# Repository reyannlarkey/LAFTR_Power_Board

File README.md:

# LAFTR_Power_Board
Eagle Files for the LAFTR power board

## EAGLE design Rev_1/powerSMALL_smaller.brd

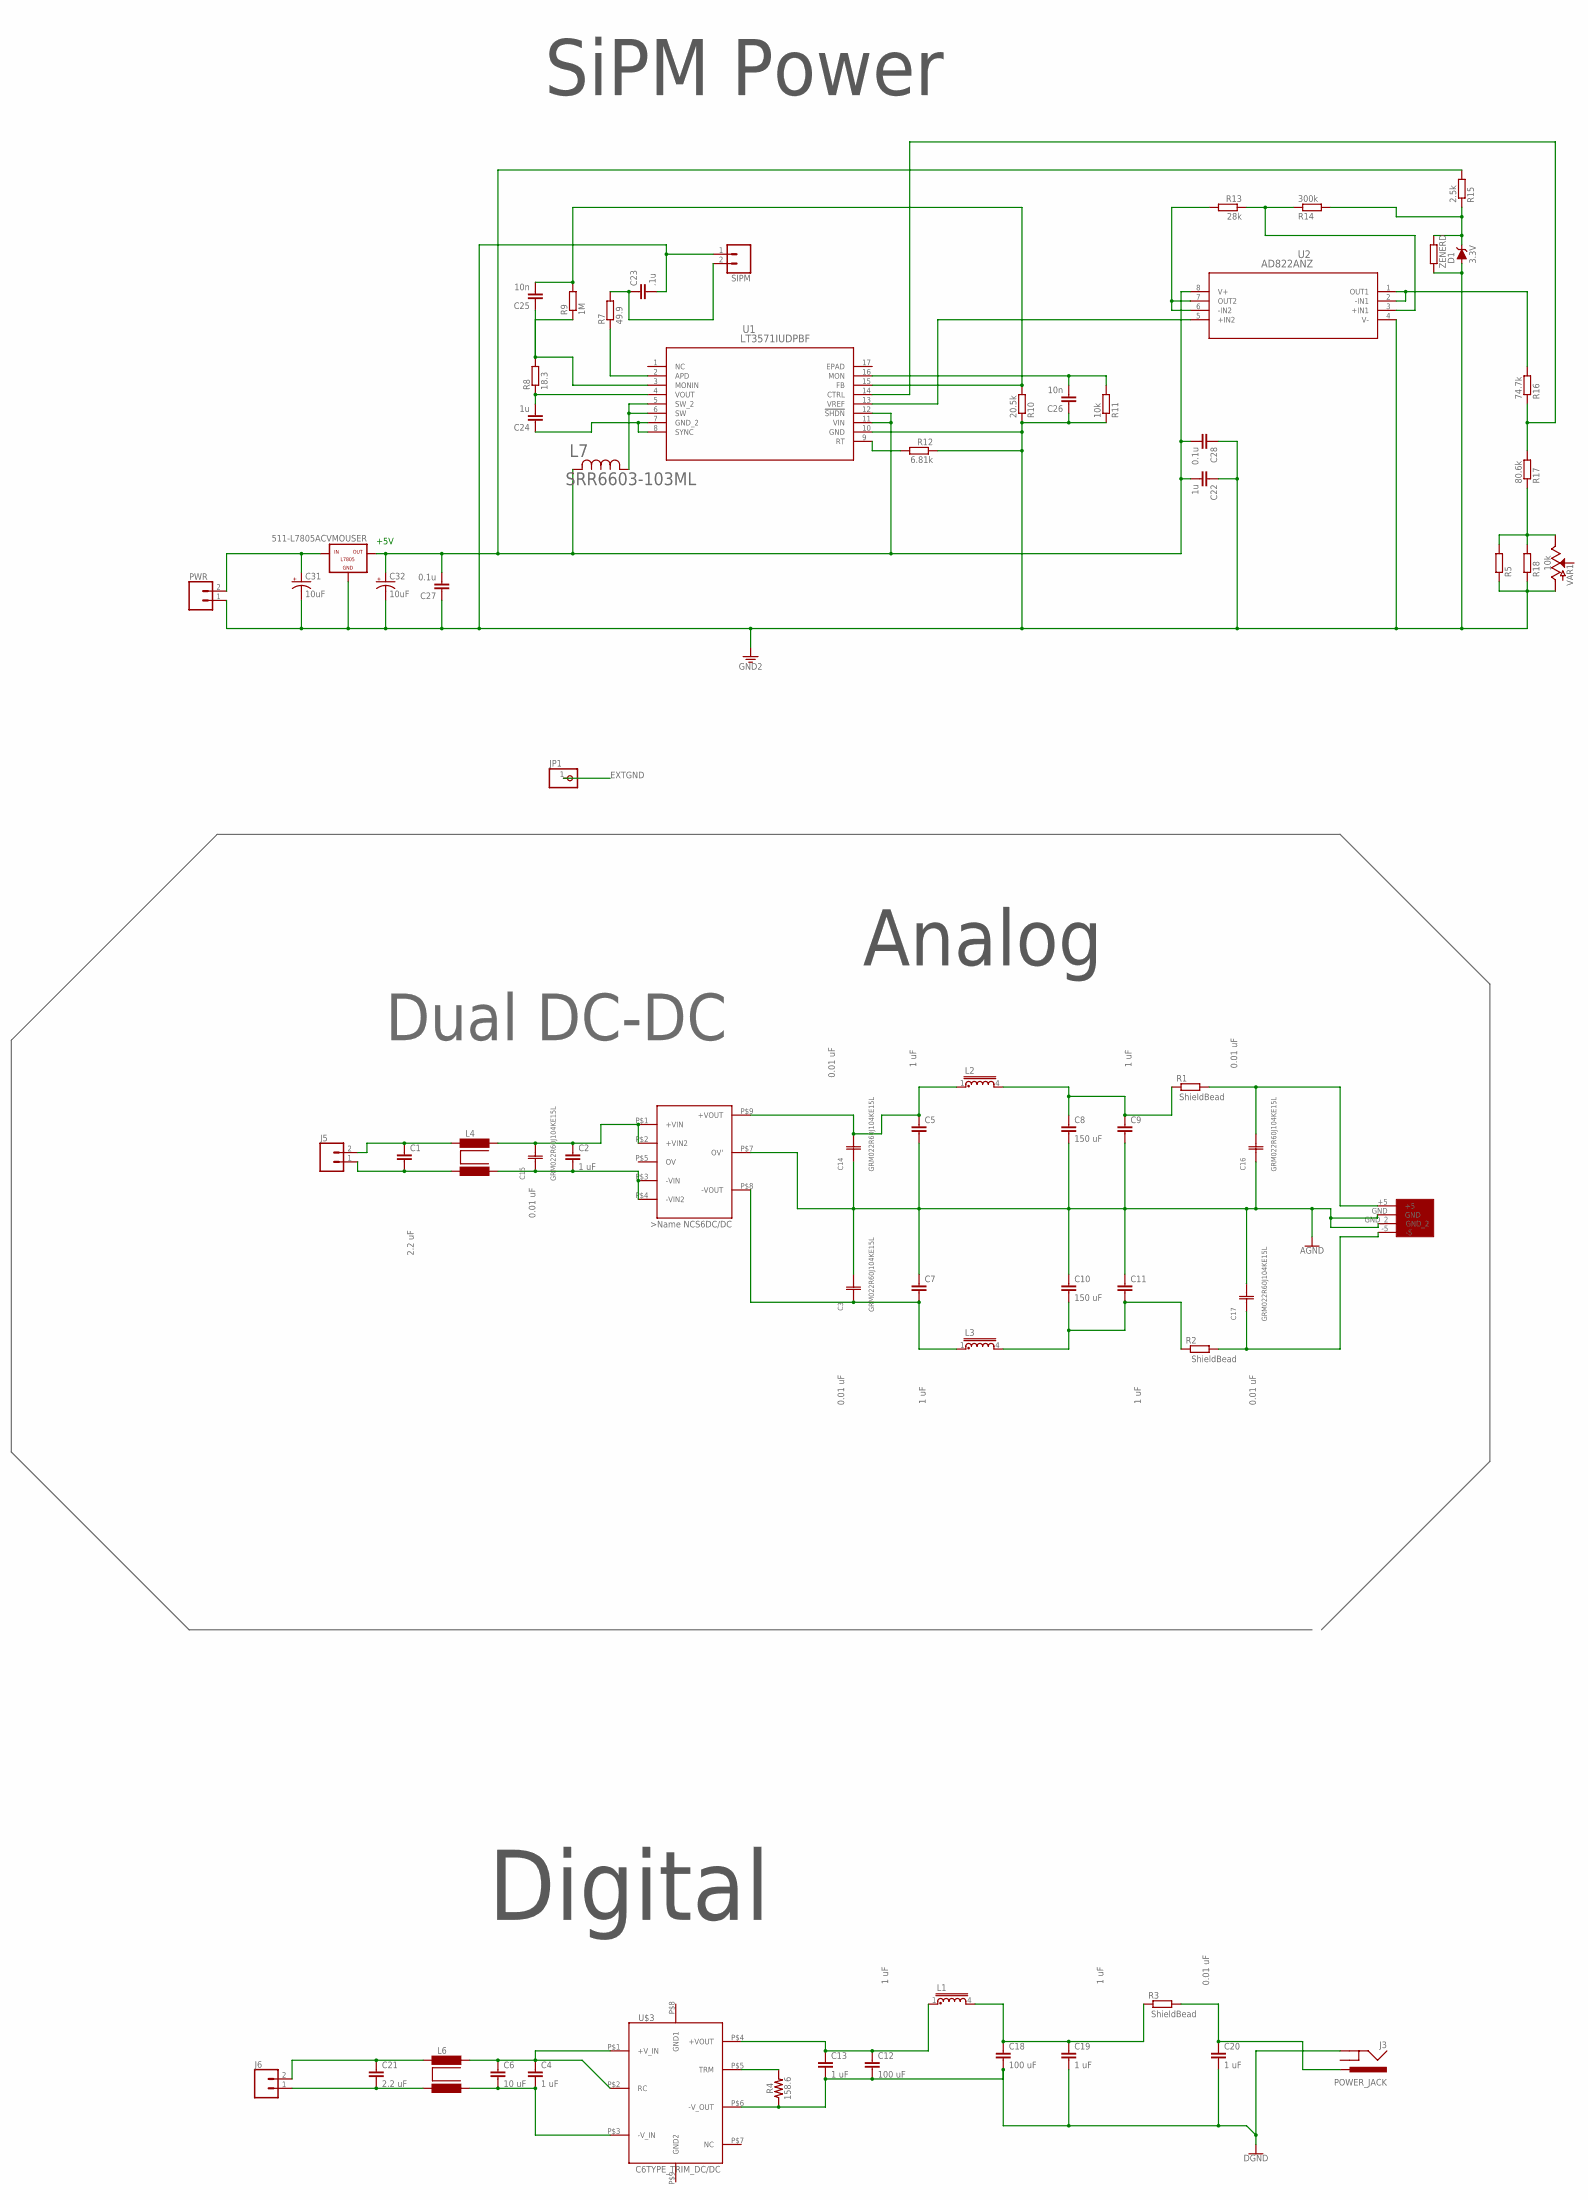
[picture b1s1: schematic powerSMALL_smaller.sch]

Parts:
511-L7805ACVMOUSER: -L7805; L7805
C1, C5, C7, C9, C11: C2.5/2; C2.5-2
C2, C4, C13, C19, C20: 1 uF; CAP-PTH-10MM
C3, C14, C15, C16, C17: GRM022R60J104KE15L; CAP_GRM02L_P42XP22
C6: 10 uF; CAP-PTH-10MM
C8, C10: 150 uF; CAP-PTH-10MM
C12, C18: 100 uF; CAP-PTH-10MM
C21: 2.2 uF; CAP-PTH-10MM
C22, C24: 1u; C2.5-2
C23: .1u; C2.5-2
C25, C26: 10n; C2.5-2
C27, C28: 0.1u; C2.5-2
C31, C32: 10uF; 0603-POLAR
D1: 3.3V; SOD-323
J3: POWER_JACK; POWER_JACK_PTH
J5, J6: CONN_02PTH4; 1X02_XTRA_BIG
JP1: PINHD-1X1; 1X01
L1, L2, L3: U15-CHOKE; U15CHOKE
L4, L6: SMR6-I; SM-R6
L7: SRR6603-103ML; IND_BOURNS_SRR6603
PWR: CONN_02PTH4; 1X02_XTRA_BIG
R1, R2, R3, R5, R18: R0207/10; 0207/10
R4: 158.6; AXIAL-0.3
R7: 49.9; 0207/10
R8: 18.3; 0207/10
R9: 1M; 0207/10
R10: 20.5k; 0207/10
R11: 10k; 0207/10
R12: 6.81k; 0207/10
R13: 28k; 0207/10
R14: 300k; 0207/10
R15: 2.5k; 0207/10
R16: 74.7k; 0207/10
R17: 80.6k; 0207/10
SIPM: CONN_02PTH4; 1X02_XTRA_BIG
U1: LT3571IUDPBF; QFN-16_UD
U2: AD822ANZ; N_8
U$1: NCS6D1205; NCS6D1205C
U$3: C6TYPE_TRIM_DC/DC; CONV/DC/DC_6W_SNGL_C6TYPE
U$4: WM403_NDPOWER_JACK; WM4302-ND
VAR1: 10k; POT-PTH-ALPS
ZENERD: R0207/10; 0207/10

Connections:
5VSUPPLY: 511-L7805ACVMOUSER.OUT, C22.2, C27.2, C28.2, C32.+, L7.2, R15.2, U1.11 (VIN), U1.12 (!SHDN), U2.8 (V+)
-FINV: C16.2 (22), R1.2, U$4.+5
AGND: C3.2 (22), C5.2, C7.1, C8.2, C9.2, C10.1, C11.1, C14.1 (11), C16.1 (11), C17.2 (22), U$1.P$7 (OV'), U$4.GND, U$4.GND_2
DGND: C12.2, C13.2, C18.2, C19.2, C20.2, J3.GND, R4.P$1 (1), U$3.P$6 (-V_OUT)
EXTGND: JP1.1
unnamed: C1.1, J5.2, L4.1
unnamed: C1.2, J5.1, L4.4
unnamed: C3.1 (11), C7.2, L3.1, U$1.P$8 (-VOUT)
unnamed: C2.1, C15.2 (22), L4.8, U$1.P$1 (+VIN), U$1.P$2 (+VIN2)
unnamed: C5.1, C14.2 (22), L2.1, U$1.P$9 (+VOUT)
unnamed: C8.1, C9.1, L2.4, R1.1
unnamed: R13.2, U2.6 (-IN2), U2.7 (OUT2)
unnamed: C10.2, C11.2, L3.4, R2.1
unnamed: C17.1 (11), R2.2, U$4.-5
unnamed: C21.1, J6.2, L6.1
unnamed: C21.2, J6.1, L6.4
unnamed: C4.1, C6.1, L6.8, U$3.P$1 (+V_IN), U$3.P$2 (RC)
unnamed: C4.2, C6.2, L6.5, U$3.P$3 (-V_IN)
unnamed: C24.2, R8.1, U1.4 (VOUT)
unnamed: C20.1, J3.PWR, R3.2
unnamed: R4.P$2 (2), U$3.P$5 (TRM)
unnamed: C18.1, C19.1, L1.4, R3.1
unnamed: C24.1, U1.7 (GND_2), U1.8 (SYNC)
unnamed: C12.1, C13.1, L1.1, U$3.P$4 (+VOUT)
unnamed: R7.1, U1.2 (APD)
unnamed: C23.1, R7.2, SIPM.2
unnamed: C25.1, R8.2, R9.1, U1.3 (MONIN)
unnamed: C26.2, R11.2, U1.16 (MON)
unnamed: L7.1, U1.5 (SW_2), U1.6 (SW)
unnamed: U1.13 (VREF), U2.5 (+IN2)
unnamed: R16.2, U2.1 (OUT1), U2.2 (-IN1)
unnamed: C25.2, R9.2, R10.2, U1.15 (FB)
unnamed: R13.1, R14.1, U2.3 (+IN1)
unnamed: R12.2, U1.9 (RT)
unnamed: D1.C, R14.2, R15.1, ZENERD.2
unnamed: R16.1, R17.2, U1.14 (CTRL)
unnamed: R5.2, R17.1, R18.2, VAR1.P$1 (E)
unnamed: C2.2, C15.1 (11), L4.5, U$1.P$3 (-VIN), U$1.P$4 (-VIN2)
unnamed: 511-L7805ACVMOUSER.IN, C31.+, PWR.2
SIPMGND: 511-L7805ACVMOUSER.GND, C22.1, C23.2, C26.1, C27.1, C28.1, C31.-, C32.-, D1.A, PWR.1, R5.1, R10.1, R11.1, R12.1, R18.1, SIPM.1, U1.10 (GND), U2.4 (V-), VAR1.P$3 (A), ZENERD.1

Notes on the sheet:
0.01 uF
2.2 uF
1 uF
ShieldBead
Dual DC-DC
Analog
Digital
SiPM Power
+5V

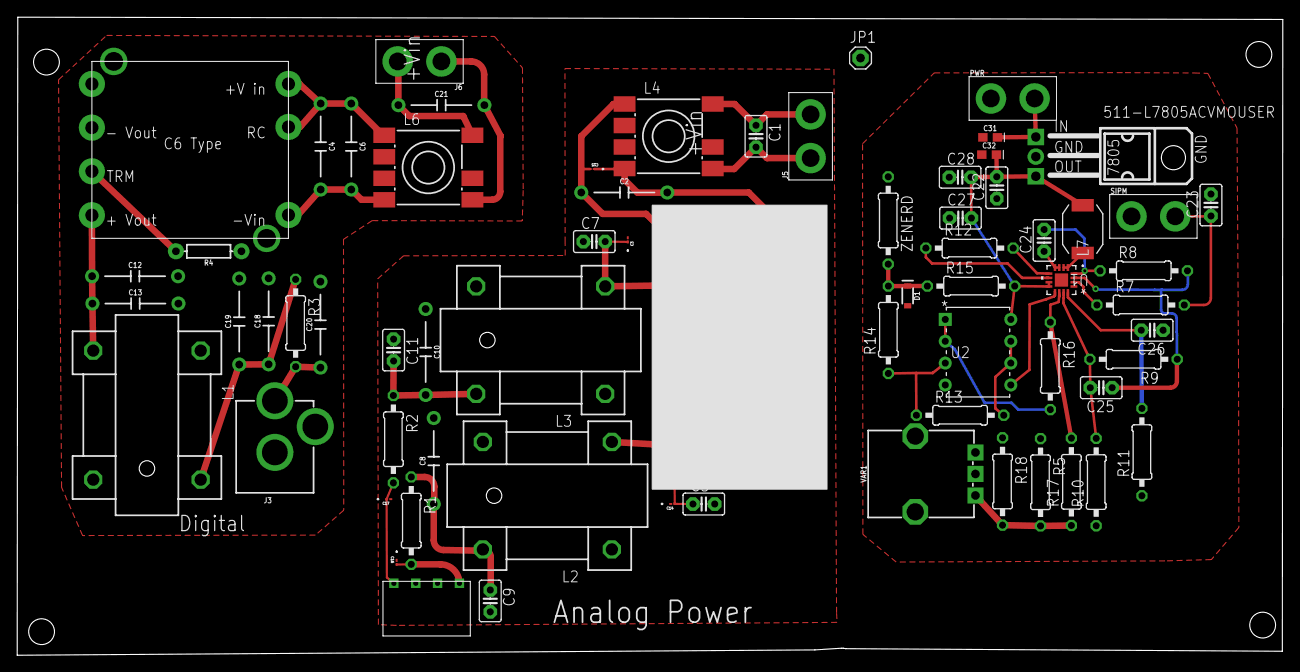
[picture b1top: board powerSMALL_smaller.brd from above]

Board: 4 copper layers, 147.2 x 74.2 mm, 68 parts (0 on the bottom side), 39 nets.

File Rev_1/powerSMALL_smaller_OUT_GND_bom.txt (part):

Partlist exported from /home/reyannlarkey/Desktop/LAFTR_POWER/powerSMALL_smaller_OUT_GND.sch at 6/26/18 3:15 PM

Qty Value              Device                          Package                   Parts                     Description                                                                                                     
4                      CONN_02PTH4                     1X02_XTRA_BIG             J5, J6, PWR, SIPM         Multi connection point. Often used as Generic Header-pin footprint for 0.1 inch spaced/style header connections 
1                      PINHD-1X1                       1X01                      JP1                       Pin header 1x1 for 0.1" spacing                                                                                 
1                      R0207/10                        0207/10                   ZENERD                    RESISTOR, European symbol                                                                                       
2                      SMR6-I                          SM-R6                     L4, L6                    CHOKE                                                                                                           
3                      U15-CHOKE                       U15CHOKE                  L1, L2, L3                CHOKE                                                                                                           
1   -L7805             -L7805                          L7805                     511-L7805ACVMOUSER                                                                                                                        
1   .1uF               C2.5/2                          C2.5-2                    C23                       CAPACITOR                                                                                                       
5   0.01uF             10NF-PTH-10MM-10000V-1-%        CAP-PTH-10MM              C2, C4, C13, C19, C20     0.01uF/10nF/10,000pF ceramic capacitors                                                                         
5   0.01uF             C-EUC0603                       C0603                     C29, C30, C33, C34, C35   CAPACITOR, European symbol                                                                                      
2   0.1uF              C2.5/2                          C2.5-2                    C27, C28                  CAPACITOR                                                                                                       
2   100uF              10NF-PTH-10MM-10000V-1-%        CAP-PTH-10MM              C12, C18                  0.01uF/10nF/10,000pF ceramic capacitors                                                                         
1   10k                POTENTIOMETER-PTH-9MM-1/20W-20% POT-PTH-ALPS              VAR1                      Potentiometer (Pot)                                                                                             
1   10k                R0207/10                        0207/10                   R11                       RESISTOR, European symbol                                                                                       
2   10nF               C2.5/2                          C2.5-2                    C25, C26                  CAPACITOR                                                                                                       
1   10uF               10NF-PTH-10MM-10000V-1-%        CAP-PTH-10MM              C6                        0.01uF/10nF/10,000pF ceramic capacitors                                                                         
2   10uF               10UF-POLAR-0603-6.3V-20%(TANT)  0603-POLAR                C31, C32                  10.0µF polarized capacitors                                                                                     
2   150 uF             10NF-PTH-10MM-10000V-1-%        CAP-PTH-10MM              C8, C10                   0.01uF/10nF/10,000pF ceramic capacitors                                                                         
1   158.6              10MOHM-HORIZ-1/4W-5%            AXIAL-0.3                 R4                        RES-09327                                                                                                       
1   18.3               R0207/10                        0207/10                   R8                        RESISTOR, European symbol                                                                                       
1   1M                 R0207/10                        0207/10                   R9                        RESISTOR, European symbol                                                                                       
6   1uF                C2.5/2                          C2.5-2                    C5, C7, C9, C11, C22, C24 CAPACITOR                                                                                                       
1   2.2uF              10NF-PTH-10MM-10000V-1-%        CAP-PTH-10MM              C21                       0.01uF/10nF/10,000pF ceramic capacitors                                                                         
1   2.2uF              C2.5/2                          C2.5-2                    C1                        CAPACITOR                                                                                                       
1   2.5k               R0207/10                        0207/10                   R15                       RESISTOR, European symbol                                                                                       
1   20.5k              R0207/10                        0207/10                   R10                       RESISTOR, European symbol                                                                                       
1   28k                R0207/10                        0207/10                   R13                       RESISTOR, European symbol                                                                                       
1   3.3V               DIODE-ZENER-MM3Z3V3T1G          SOD-323                   D1                        Zener Diode                                                                                                     
1   300k               R0207/10                        0207/10                   R14                       RESISTOR, European symbol                                                                                       
1   49.9               R0207/10                        0207/10                   R7                        RESISTOR, European symbol                                                                                       
1   6.81k              R0207/10                        0207/10                   R12                       RESISTOR, European symbol                                                                                       
1   74.7k              R0207/10                        0207/10                   R16                       RESISTOR, European symbol                                                                                       
1   80.6k              R0207/10                        0207/10                   R17                       RESISTOR, European symbol                                                                                       
1   AD822ANZ           AD822ANZ                        N_8                       U2                                                                                                                                        
1   C6TYPE_TRIM_DC/DC  C6TYPE_TRIM_DC/DC               CONV/DC/DC_6W_SNGL_C6TYPE U$3                                                                                                                                       
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
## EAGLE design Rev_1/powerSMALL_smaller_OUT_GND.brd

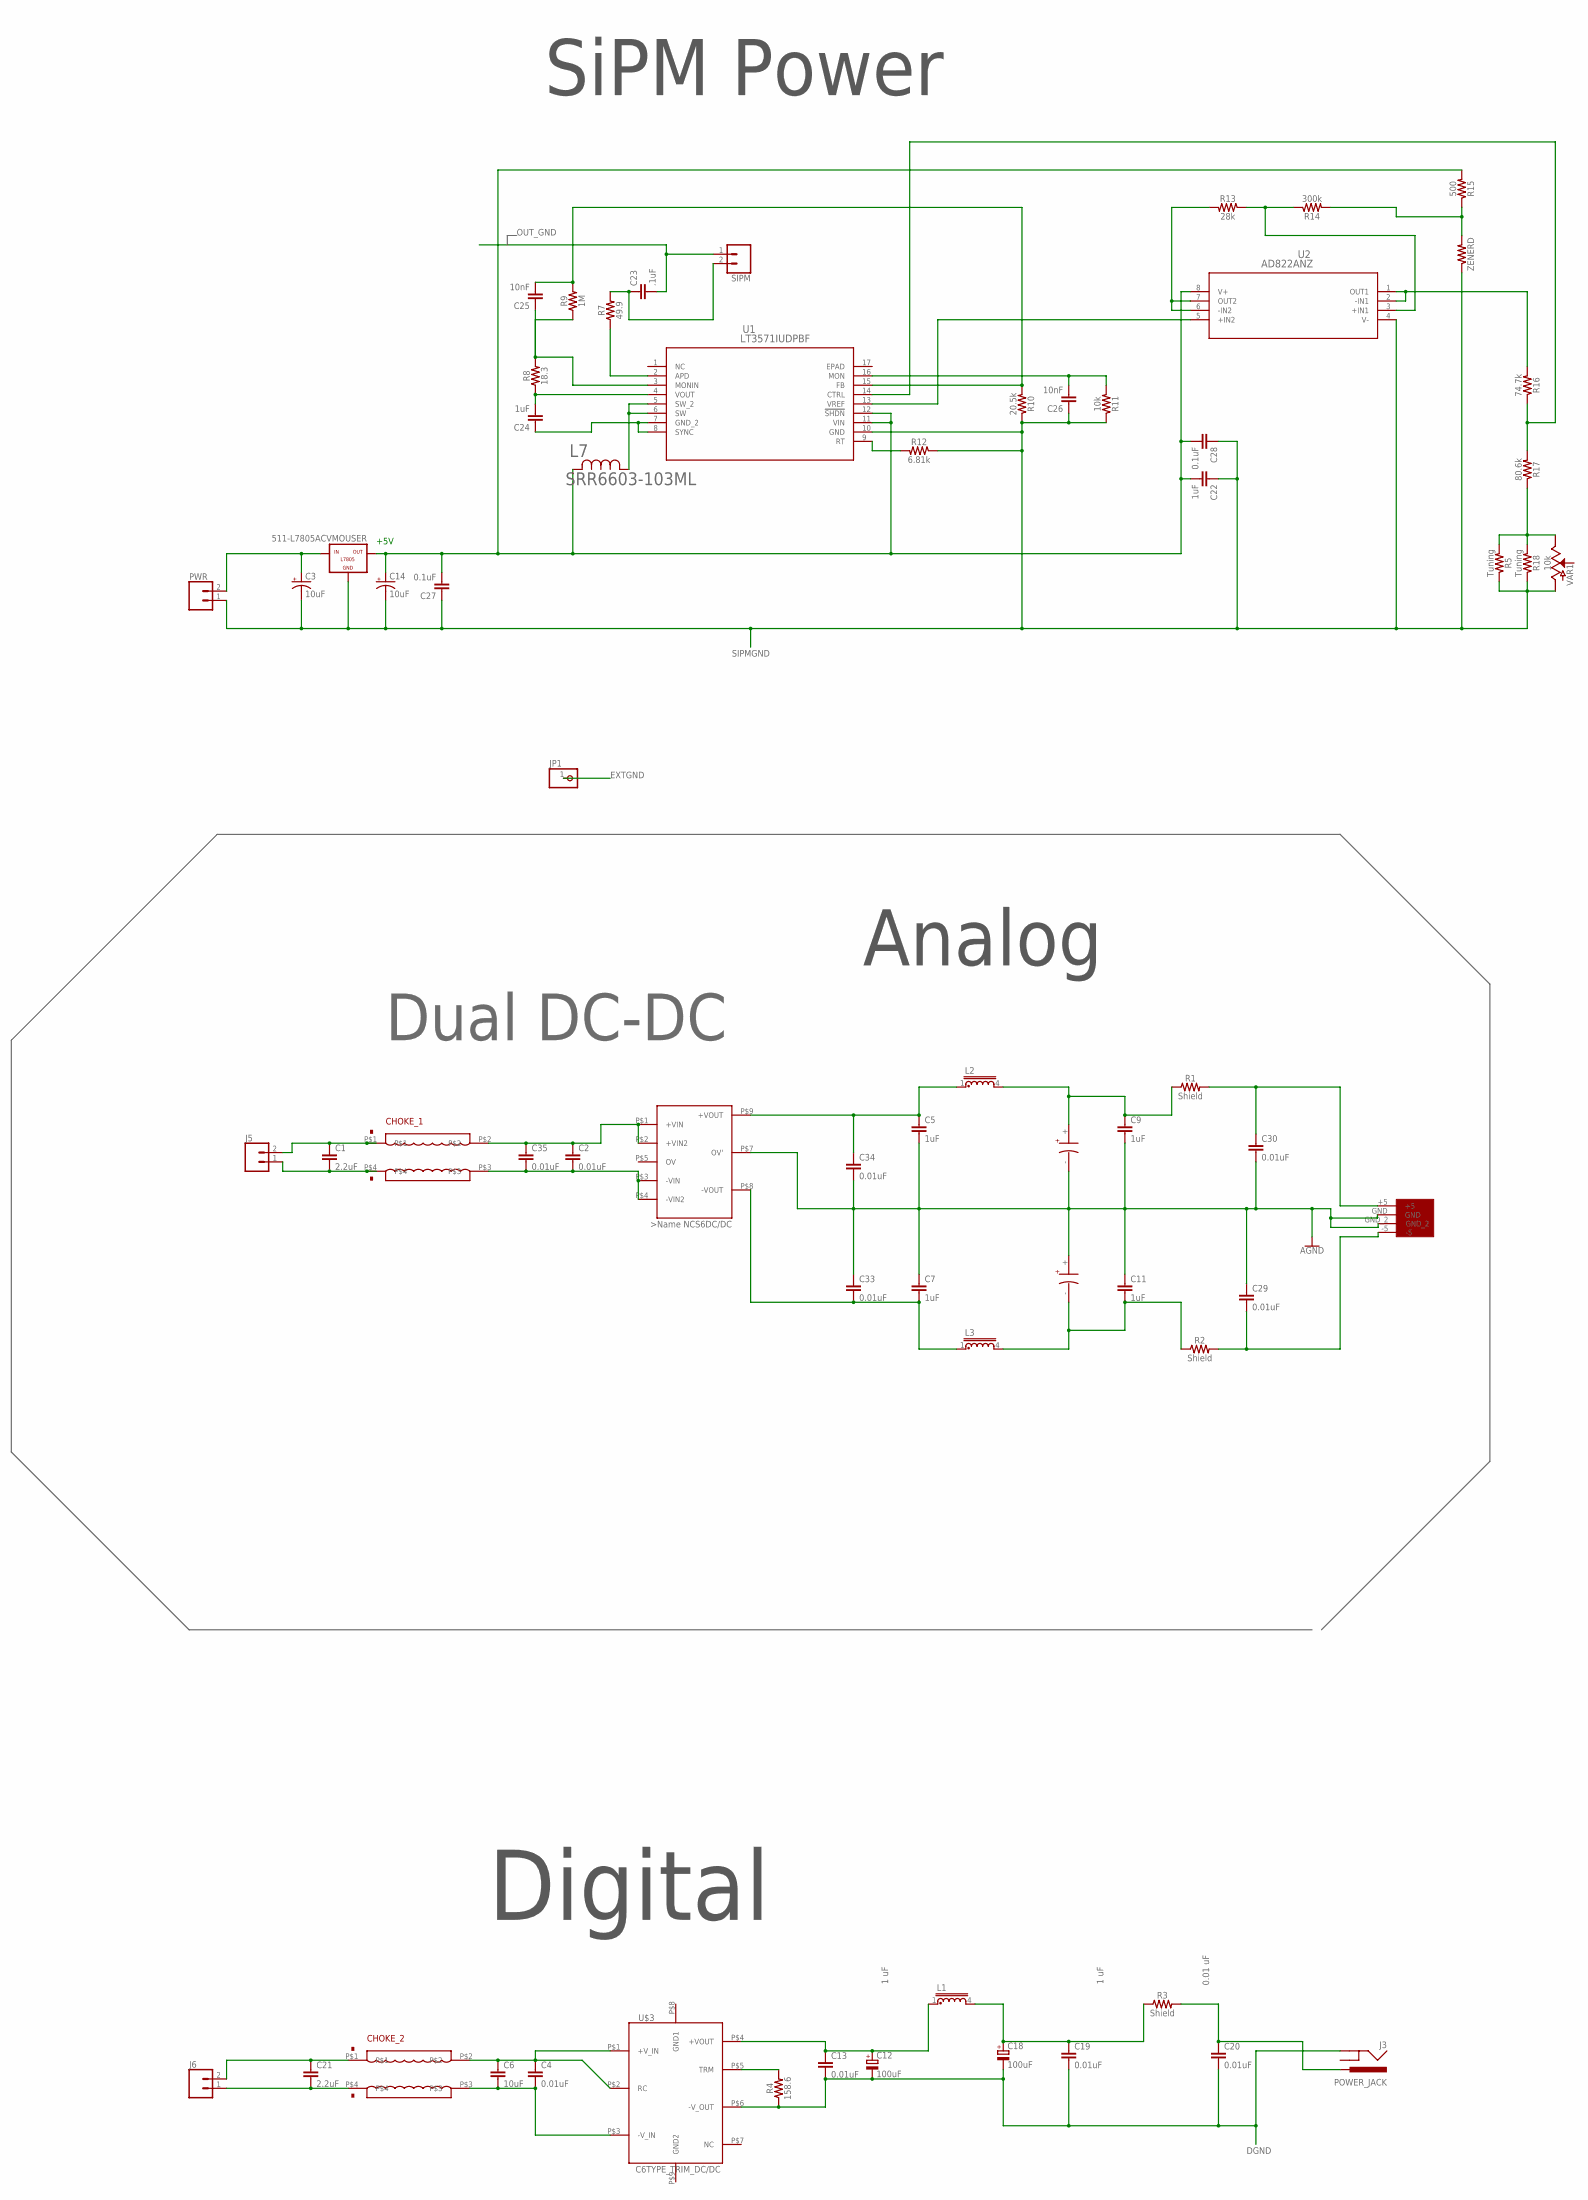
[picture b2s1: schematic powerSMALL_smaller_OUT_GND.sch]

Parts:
511-L7805ACVMOUSER: -L7805; L7805
C1, C21: 2.2uF; C050-024X044
C2, C4, C13, C19, C20: 0.01uF; C025-025X050
C3, C14: 10uF; T/3528-12R
C5, C7, C9, C11, C22, C24: 1uF; C025-025X050
C6: 10uF; C025-025X050
C8, C10: 150uF; 399-3567-ND150UF
C12, C18: 100uF; C/6032-28R
C23: .1uF; C2.5-2
C25, C26: 10nF; C2.5-2
C27, C28: 0.1uF; C2.5-2
C29, C30, C33, C34, C35: 0.01uF; C0603
CHOKE_1, CHOKE_2: DN4730-ND
J3: POWER_JACK; POWER_JACK_PTH
J5, J6: CONN_02PTH4; 1X02_XTRA_BIG
JP1: PINHD-1X1; 1X01
L1, L2, L3: U15-CHOKE; U15CHOKE
L7: SRR6603-103ML; IND_BOURNS_SRR6603
PWR: CONN_02PTH4; 1X02_XTRA_BIG
PWR_JACK: WM403_NDPOWER_JACK; WM4302-ND
R1, R2, R3: Shield; AXIAL-0.3
R4: 158.6; AXIAL-0.3
R5, R18: Tuning; AXIAL-0.3
R7: 49.9; AXIAL-0.3
R8: 18.3; AXIAL-0.3
R9: 1M; AXIAL-0.3
R10: 20.5k; AXIAL-0.3
R11: 10k; AXIAL-0.3
R12: 6.81k; AXIAL-0.3
R13: 28k; AXIAL-0.3
R14: 300k; AXIAL-0.3
R15: 500; AXIAL-0.3
R16: 74.7k; AXIAL-0.3
R17: 80.6k; AXIAL-0.3
SIPM: CONN_02PTH4; 1X02_XTRA_BIG
U1: LT3571IUDPBF; QFN-16_UD
U2: AD822ANZ; N_8
U$1: NCS6D1205; NCS6D1205C
U$3: C6TYPE_TRIM_DC/DC; CONV/DC/DC_6W_SNGL_C6TYPE
VAR1: 10k; POT-PTH-ALPS
ZENERD: AXIAL-0.3

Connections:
5VSUPPLY: 511-L7805ACVMOUSER.OUT, C14.+, C22.2, C27.2, C28.2, L7.2, R15.P$2 (2), U1.11 (VIN), U1.12 (!SHDN), U2.8 (V+)
-FINV: C30.1, PWR_JACK.+5, R1.P$2 (2)
AGND: C5.2, C7.1, C8.- (N), C9.2, C10.+, C11.1, C29.1, C30.2, C33.1, C34.2, PWR_JACK.GND, PWR_JACK.GND_2, U$1.P$7 (OV')
DGND: C12.-, C13.2, C18.-, C19.2, C20.2, J3.GND, R4.P$1 (1), U$3.P$6 (-V_OUT)
EXTGND: JP1.1
unnamed: C1.1, CHOKE_1.P$1, J5.2
unnamed: C1.2, CHOKE_1.P$4, J5.1
unnamed: C7.2, C33.2, L3.1, U$1.P$8 (-VOUT)
unnamed: C2.1, C35.1, CHOKE_1.P$2, U$1.P$1 (+VIN), U$1.P$2 (+VIN2)
unnamed: C8.+, C9.1, L2.4, R1.P$1 (1)
unnamed: R13.P$2 (2), U2.6 (-IN2), U2.7 (OUT2)
unnamed: C10.- (N), C11.2, L3.4, R2.P$1 (1)
unnamed: C29.2, PWR_JACK.-5, R2.P$2 (2)
unnamed: C21.1, CHOKE_2.P$1, J6.2
unnamed: C21.2, CHOKE_2.P$4, J6.1
unnamed: C4.1, C6.1, CHOKE_2.P$2, U$3.P$1 (+V_IN), U$3.P$2 (RC)
unnamed: C4.2, C6.2, CHOKE_2.P$3, U$3.P$3 (-V_IN)
unnamed: C24.2, R8.P$1 (1), U1.4 (VOUT)
unnamed: C20.1, J3.PWR, R3.P$2 (2)
unnamed: R4.P$2 (2), U$3.P$5 (TRM)
unnamed: C18.+, C19.1, L1.4, R3.P$1 (1)
unnamed: C24.1, U1.7 (GND_2), U1.8 (SYNC)
unnamed: C12.+, C13.1, L1.1, U$3.P$4 (+VOUT)
unnamed: R7.P$1 (1), U1.2 (APD)
unnamed: C23.1, R7.P$2 (2), SIPM.2
unnamed: C25.1, R8.P$2 (2), R9.P$1 (1), U1.3 (MONIN)
unnamed: C26.2, R11.P$2 (2), U1.16 (MON)
unnamed: L7.1, U1.5 (SW_2), U1.6 (SW)
unnamed: U1.13 (VREF), U2.5 (+IN2)
unnamed: C5.1, C34.1, L2.1, U$1.P$9 (+VOUT)
unnamed: R16.P$2 (2), U2.1 (OUT1), U2.2 (-IN1)
unnamed: C25.2, R9.P$2 (2), R10.P$2 (2), U1.15 (FB)
unnamed: R13.P$1 (1), R14.P$1 (1), U2.3 (+IN1)
unnamed: R12.P$2 (2), U1.9 (RT)
unnamed: R14.P$2 (2), R15.P$1 (1), ZENERD.P$2 (2)
unnamed: R16.P$1 (1), R17.P$2 (2), U1.14 (CTRL)
unnamed: R5.P$2 (2), R17.P$1 (1), R18.P$2 (2), VAR1.P$1 (E)
unnamed: C2.2, C35.2, CHOKE_1.P$3, U$1.P$3 (-VIN), U$1.P$4 (-VIN2)
unnamed: 511-L7805ACVMOUSER.IN, C3.+, PWR.2
OUT_GND: C23.2, SIPM.1
SIPMGND: 511-L7805ACVMOUSER.GND, C3.-, C14.-, C22.1, C26.1, C27.1, C28.1, PWR.1, R5.P$1 (1), R10.P$1 (1), R11.P$1 (1), R12.P$1 (1), R18.P$1 (1), U1.10 (GND), U2.4 (V-), VAR1.P$3 (A), ZENERD.P$1 (1)

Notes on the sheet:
Dual DC-DC
0.01 uF
1 uF
Analog
Digital
SiPM Power
+5V

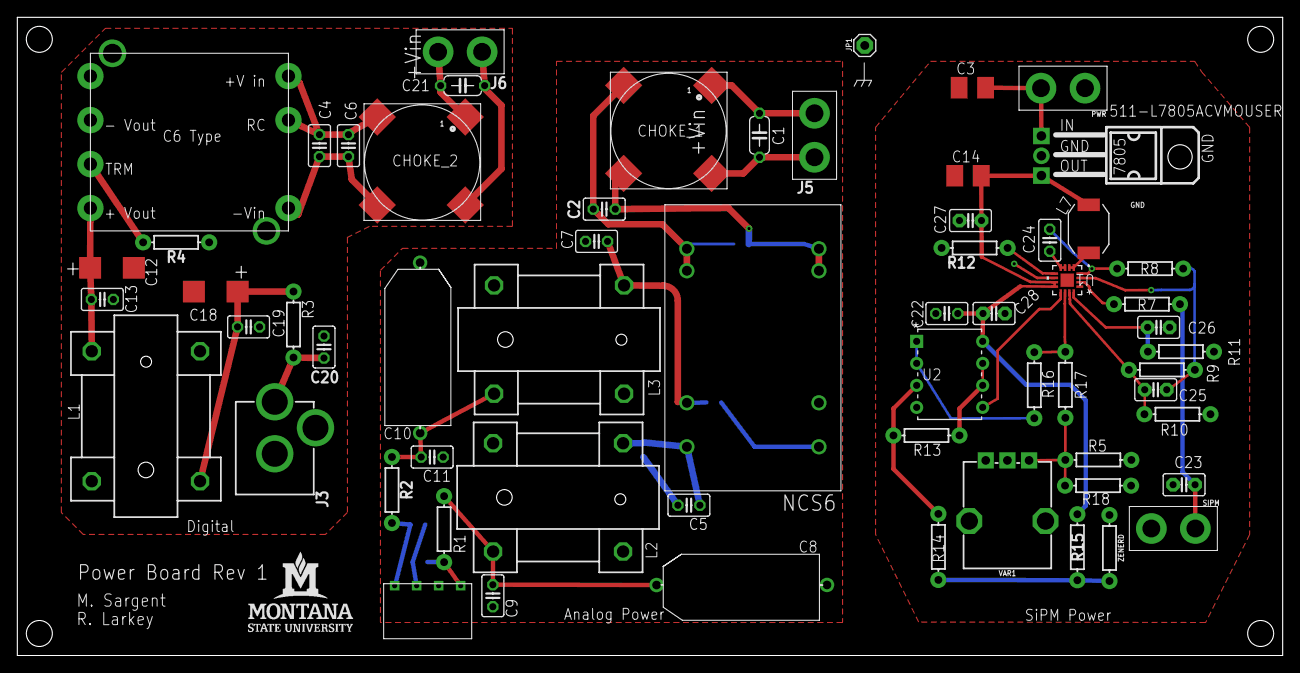
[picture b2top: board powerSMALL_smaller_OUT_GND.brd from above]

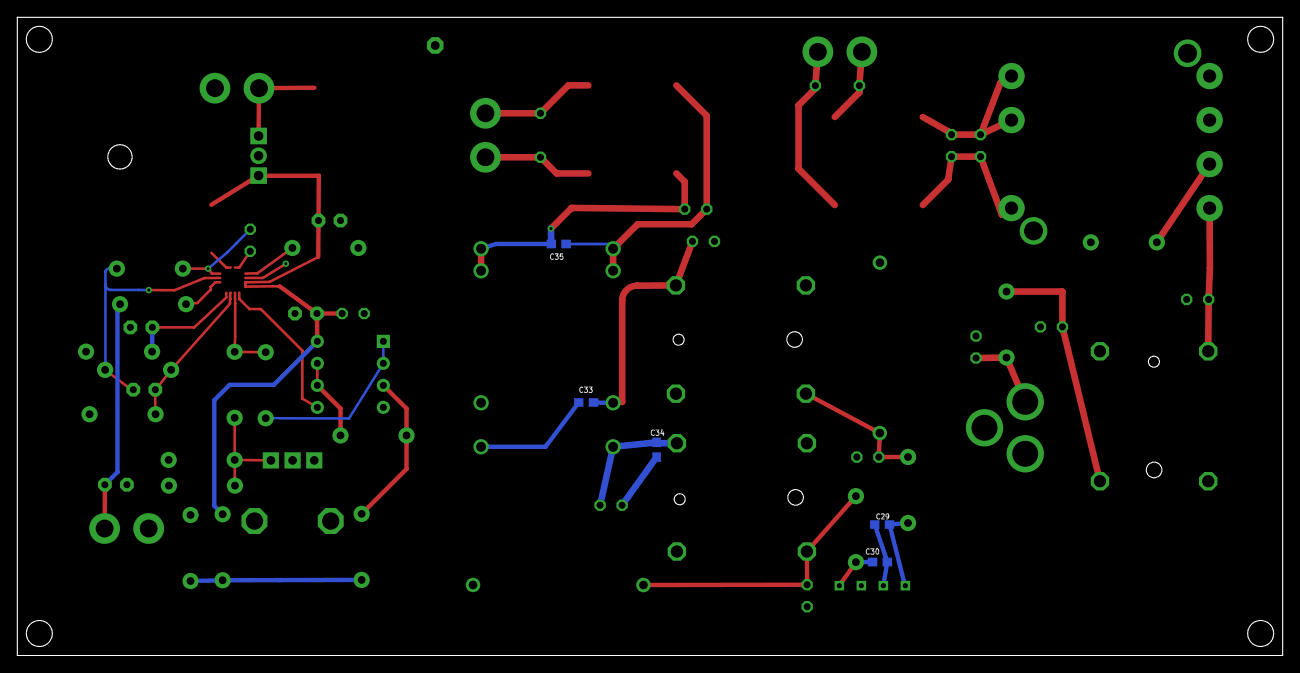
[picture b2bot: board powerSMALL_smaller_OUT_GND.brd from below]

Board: 4 copper layers, 146.1 x 73.7 mm, 67 parts (5 on the bottom side), 40 nets.

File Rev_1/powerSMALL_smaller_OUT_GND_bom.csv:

"Qty";"Value";"Device";"Package";"Parts";"Description";"MANUFACTURER_PART_NUMBER";"MF";"MPN";"OC_FARNELL";"OC_NEWARK";"PROD_ID";"SF_SKU";"SPICEMODEL";"SPICEPREFIX";"VALUE";"VENDOR";
"4";"";"CONN_02PTH4";"1X02_XTRA_BIG";"J5, J6, PWR, SIPM";"Multi connection point. Often used as Generic Header-pin footprint for 0.1 inch spaced/style header connections";"";"";"";"";"unknown";"";"";"";"";"";"";
"1";"";"PINHD-1X1";"1X01";"JP1";"Pin header 1x1 for 0.1" spacing";"";"";"";"";"unknown";"";"";"";"";"";"";
"1";"";"R0207/10";"0207/10";"ZENERD";"RESISTOR, European symbol";"";"";"";"";"unknown";"";"";"NONE";"R";"";"";
"2";"";"SMR6-I";"SM-R6";"L4, L6";"CHOKE";"";"";"";"unknown";"unknown";"";"";"";"";"";"";
"3";"";"U15-CHOKE";"U15CHOKE";"L1, L2, L3";"CHOKE";"";"";"";"unknown";"unknown";"";"";"";"";"";"";
"1";"-L7805";"-L7805";"L7805";"511-L7805ACVMOUSER";"";"";"";"";"";"unknown";"";"";"";"";"";"";
"1";".1uF";"C2.5/2";"C2.5-2";"C23";"CAPACITOR";"";"";"";"";"unknown";"";"";"";"";"";"";
"1";"0.01uF";"C-EU025-024X044";"C025-024X044";"C2";"CAPACITOR, European symbol";"";"";"";"";"unknown";"";"";"";"";"";"";
"4";"0.01uF";"C-EU025-025X050";"C025-025X050";"C4, C13, C19, C20";"CAPACITOR, European symbol";"";"";"";"";"unknown";"";"";"";"";"";"";
"5";"0.01uF";"C-EUC0603";"C0603";"C29, C30, C33, C34, C35";"CAPACITOR, European symbol";"";"";"";"";"";"";"";"";"";"";"";
"2";"0.1uF";"C2.5/2";"C2.5-2";"C27, C28";"CAPACITOR";"";"";"";"";"unknown";"";"";"";"";"";"";
"2";"100uF";"C-EU025-025X050";"C025-025X050";"C12, C18";"CAPACITOR, European symbol";"";"";"";"";"unknown";"";"";"";"";"";"";
"1";"10k";"POTENTIOMETER-PTH-9MM-1/20W-20%";"POT-PTH-ALPS";"VAR1";"Potentiometer (Pot)";"";"";"";"";"unknown";"RES-09177";"COM-09288";"";"";"10k";"";
"1";"10k";"R0207/10";"0207/10";"R11";"RESISTOR, European symbol";"";"";"";"";"unknown";"";"";"NONE";"R";"";"";
"2";"10nF";"C2.5/2";"C2.5-2";"C25, C26";"CAPACITOR";"";"";"";"";"unknown";"";"";"";"";"";"";
"2";"10uF";"10UF-POLAR-0603-6.3V-20%(TANT)";"0603-POLAR";"C31, C32";"10.0µF polarized capacitors";"";"";"";"";"unknown";"CAP-13210";"";"";"";"10uF";"";
"1";"10uF";"C-EU025-025X050";"C025-025X050";"C6";"CAPACITOR, European symbol";"";"";"";"";"unknown";"";"";"";"";"";"";
"2";"150 uF";"C-EU025-025X050";"C025-025X050";"C8, C10";"CAPACITOR, European symbol";"";"";"";"";"unknown";"";"";"";"";"";"";
"1";"158.6";"10MOHM-HORIZ-1/4W-5%";"AXIAL-0.3";"R4";"RES-09327";"";"";"";"";"unknown";"RES-09327";"";"";"";"10M";"";
"1";"18.3";"R0207/10";"0207/10";"R8";"RESISTOR, European symbol";"";"";"";"";"unknown";"";"";"NONE";"R";"";"";
"1";"1M";"R0207/10";"0207/10";"R9";"RESISTOR, European symbol";"";"";"";"";"unknown";"";"";"NONE";"R";"";"";
"6";"1uF";"C2.5/2";"C2.5-2";"C5, C7, C9, C11, C22, C24";"CAPACITOR";"";"";"";"";"unknown";"";"";"";"";"";"";
"1";"2.2uF";"C-EU025-025X050";"C025-025X050";"C21";"CAPACITOR, European symbol";"";"";"";"";"unknown";"";"";"";"";"";"";
"1";"2.2uF";"C2.5/2";"C2.5-2";"C1";"CAPACITOR";"";"";"";"";"unknown";"";"";"";"";"";"";
"1";"2.5k";"R0207/10";"0207/10";"R15";"RESISTOR, European symbol";"";"";"";"";"unknown";"";"";"NONE";"R";"";"";
"1";"20.5k";"R0207/10";"0207/10";"R10";"RESISTOR, European symbol";"";"";"";"";"unknown";"";"";"NONE";"R";"";"";
"1";"28k";"R0207/10";"0207/10";"R13";"RESISTOR, European symbol";"";"";"";"";"unknown";"";"";"NONE";"R";"";"";
"1";"3.3V";"DIODE-ZENER-MM3Z3V3T1G";"SOD-323";"D1";"Zener Diode";"";"";"";"";"unknown";"DIO-11284";"";"";"";"3.3V";"";
"1";"300k";"R0207/10";"0207/10";"R14";"RESISTOR, European symbol";"";"";"";"";"unknown";"";"";"NONE";"R";"";"";
"1";"49.9";"R0207/10";"0207/10";"R7";"RESISTOR, European symbol";"";"";"";"";"unknown";"";"";"NONE";"R";"";"";
"1";"6.81k";"R0207/10";"0207/10";"R12";"RESISTOR, European symbol";"";"";"";"";"unknown";"";"";"NONE";"R";"";"";
"1";"74.7k";"R0207/10";"0207/10";"R16";"RESISTOR, European symbol";"";"";"";"";"unknown";"";"";"NONE";"R";"";"";
"1";"80.6k";"R0207/10";"0207/10";"R17";"RESISTOR, European symbol";"";"";"";"";"unknown";"";"";"NONE";"R";"";"";
"1";"AD822ANZ";"AD822ANZ";"N_8";"U2";"";"AD822ANZ";"";"";"";"unknown";"";"";"";"";"";"Analog Devices Inc";
"1";"C6TYPE_TRIM_DC/DC";"C6TYPE_TRIM_DC/DC";"CONV/DC/DC_6W_SNGL_C6TYPE";"U$3";"";"";"";"";"";"unknown";"";"";"";"";"";"";
"1";"LT3571IUDPBF";"LT3571IUDPBF";"QFN-16_UD";"U1";"";"LT3571IUD#PBF";"";"";"";"unknown";"";"";"";"";"";"Linear Technology";
"1";"NCS6D1205";"NCS6D1205";"NCS6D1205C";"U$1";"";"";"";"";"";"unknown";"";"";"";"";"";"";
"1";"POWER_JACK";"POWER_JACK";"POWER_JACK_PTH";"J3";"Power Jack Connector";"";"";"";"";"unknown";"CONN-08197";"";"";"";"";"";
"1";"SRR6603-103ML";"SRR6603-103ML";"IND_BOURNS_SRR6603";"L7";"";"SRR6603103ML";"";"";"";"unknown";"";"";"";"";"";"Bourns Electronics";
"3";"Shield";"R0207/10";"0207/10";"R1, R2, R3";"RESISTOR, European symbol";"";"";"";"";"unknown";"";"";"NONE";"R";"";"";
"2";"Tuning";"R0207/10";"0207/10";"R5, R18";"RESISTOR, European symbol";"";"";"";"";"unknown";"";"";"NONE";"R";"";"";
"1";"WM403_NDPOWER_JACK";"WM403_NDPOWER_JACK";"WM4302-ND";"PWR_JACK";"";"";"";"";"";"unknown";"";"";"";"";"";"";

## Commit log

2018-08-13 Added Rev_2 board and schemeatic
2018-08-13 Added board and Schematic for Rev_2
2018-08-13 Saw that there was a mistake in jumper ports--> fixed it
2018-08-13 Created the OshPark Files
2018-08-13 Added all the stuff and ordered the boards

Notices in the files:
parts and their libraries:
SparkFun-Capacitors: Licensing: Creative Commons ShareAlike 4.0 International - https://creativecommons.org/licenses/by-sa/4.0
